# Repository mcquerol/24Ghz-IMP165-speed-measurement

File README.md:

##24ghz-imp165-speed-measurement

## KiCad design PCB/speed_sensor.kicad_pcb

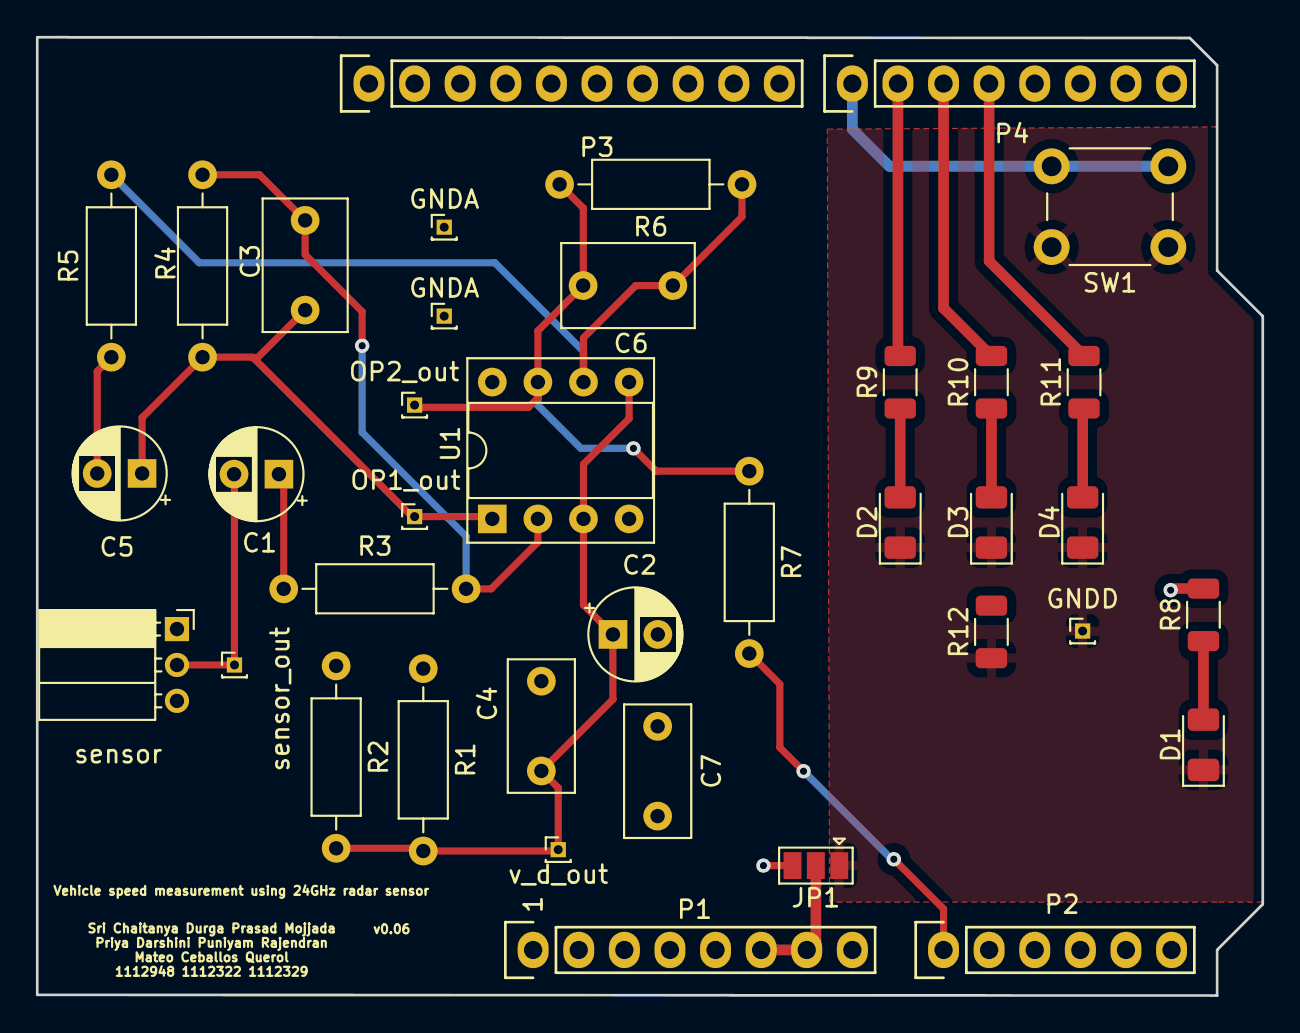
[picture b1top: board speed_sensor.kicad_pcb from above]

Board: 4 copper layers, 68.3 x 53.4 mm, 38 parts (0 on the bottom side), 21 nets.

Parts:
C1, C5: 4.7u; CP_Radial_D5.0mm_P2.50mm
C2: 22u; CP_Radial_D5.0mm_P2.50mm
C3: 1.5n; C_Rect_L7.2mm_W4.5mm_P5.00mm_FKS2_FKP2_MKS2_MKP2
C4, C7: 100n; C_Rect_L7.2mm_W3.5mm_P5.00mm_FKS2_FKP2_MKS2_MKP2
C6: 3.3n; C_Rect_L7.2mm_W4.5mm_P5.00mm_FKS2_FKP2_MKS2_MKP2
D1, D2: Red LED; LED_1206_3216Metric
D3: Yellow LED; LED_1206_3216Metric
D4: Green LED; LED_1206_3216Metric
GNDA: GNDA; PinHeader_1x01_P1.00mm_Vertical
GNDA#2: GNDA; PinHeader_1x01_P1.00mm_Vertical
GNDD: GNDD; PinHeader_1x01_P1.00mm_Vertical
JP1: SolderJumper; SolderJumper-3_P1.3mm_Open_Pad1.0x1.5mm
OP1_out: OP1_output; PinHeader_1x01_P1.00mm_Vertical
OP2_out: OP2_output; PinHeader_1x01_P1.00mm_Vertical
P1: Power; Socket_Strip_Arduino_1x08
P2: Analog; Socket_Strip_Arduino_1x06
P3: Digital; Socket_Strip_Arduino_1x10
P4: Digital; Socket_Strip_Arduino_1x08
R1, R2: 1k; R_Axial_DIN0207_L6.3mm_D2.5mm_P10.16mm_Horizontal
R3: 2.2k; R_Axial_DIN0207_L6.3mm_D2.5mm_P10.16mm_Horizontal
R4: 220k; R_Axial_DIN0207_L6.3mm_D2.5mm_P10.16mm_Horizontal
R5: 33k; R_Axial_DIN0207_L6.3mm_D2.5mm_P10.16mm_Horizontal
R6: 100k; R_Axial_DIN0207_L6.3mm_D2.5mm_P10.16mm_Horizontal
R7: 100; R_Axial_DIN0207_L6.3mm_D2.5mm_P10.16mm_Horizontal
R8, R9, R10, R11: 470; R_1206_3216Metric
R12: 10k; R_1206_3216Metric
SW1: SW_Push; SW_PUSH_6mm_H5mm
U1: LMV358; DIP-8_W7.62mm_Socket
sensor: data; PinSocket_1x03_P2.00mm_Horizontal
sensor_out: sensor_output; PinHeader_1x01_P1.00mm_Vertical
v_d_out: v_d_out; PinHeader_1x01_P1.00mm_Vertical

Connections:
+5V: C7.2, P1.5, R1.1, R8.2, U1.8 (V+), sensor.3
/A0: P2.1, R7.2
/D4: P4.4, R11.2
/D5: P4.3, R10.2
/D6: P4.2, R9.2
/D7: P4.1, SW1.2
/V_IN: C1.2, sensor.2, sensor_out.1
/v_cm: C2.1, C4.1, R1.2, R2.2, U1.3 (+), U1.5 (+), v_d_out.1
GND: JP1.2 (C), P1.6, P1.7
GNDA: C2.2, C4.2, C7.1, GNDA.1, GNDA#2.1, JP1.3 (B), R2.1, U1.4 (V-), sensor.1
GNDD: D1.1 (K), D2.1 (K), D3.1 (K), D4.1 (K), GNDD.1, JP1.1 (A), R12.1, SW1.1
unnamed: C1.1, R3.1
unnamed: C3.1, R3.2, R4.1, U1.2 (-)
unnamed: C3.2, C5.1, OP1_out.1, R4.2, U1.1
unnamed: C5.2, R5.1
unnamed: C6.1, R5.2, R6.1, U1.6 (-)
unnamed: C6.2, OP2_out.1, R6.2, R7.1, U1.7
unnamed: D1.2 (A), R8.1
unnamed: D2.2 (A), R9.1
unnamed: D3.2 (A), R10.1
unnamed: D4.2 (A), R11.1

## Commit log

2022-06-28 added REPORT and its contents
2023-01-03 added PCB and its contents
2023-07-31 added CODE and its contents
2023-08-02 added PPT and its contents
2023-08-03 Separated code into files
2023-08-03 added Datasheets
2023-08-03 Project info
2023-08-09 added LTSpice Simulation AC Sweep
2024-08-20 Add MIT License
2024-08-23 Add CC BY 4.0 License
2024-08-23 Remove CC BY 4.0 License
2024-08-23 Remove existing LICENSE file
2024-08-23 Add new LICENSE file
2024-11-05 Update LICENSE
2024-12-17 updated LICENSE
2024-12-18 added LICENSE
2026-04-07 Change header level in README.md
2026-04-07 Modify .gitattributes for KiCad file detection
    Updated KiCad file attributes to improve language detection.
2026-04-07 Update .gitattributes for KiCad file detection
2026-04-07 Modify KiCad file detection in .gitattributes
    Updated KiCad file detection settings in .gitattributes.
2026-04-07 Update .gitattributes for kicad_sym file detection
2026-04-07 Modify .gitattributes for KiCad file detection
    Updated .gitattributes to include and exclude specific KiCad files for GitHub detection.
2026-04-07 Update .gitattributes for KiCad file detection
    Changed linguist-detectable setting for .kicad_sch files.
2026-04-07 Modify .gitattributes for file detection improvements
    Updated .gitattributes to improve file detection settings for KiCad files and adjust generated source folder settings.
2026-04-07 Refactor .gitattributes to improve file handling
2026-04-07 Update .gitattributes to include ErikaOS_v2_5_3
2026-04-07 Modify linguist detection for KiCad files
    Updated .gitattributes to change linguist detection settings for KiCad files.
2026-04-07 Modify KiCad file detection settings in .gitattributes
    Updated .gitattributes to change detection settings for KiCad files.
2026-04-07 Exclude KiCad auxiliary files from linguist stats
    Change KiCad auxiliary files to be excluded from stats.
2026-04-08 Change linguist attributes for generated files
2026-04-08 Update .gitattributes for assembly file detection
    Change assembly file handling to be detectable instead of vendored.
2026-04-09 Update .gitattributes to change file detection settings
